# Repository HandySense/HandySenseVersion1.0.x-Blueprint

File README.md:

- 📫 VDO สอนใช้งาน HandySense: ...
[VDO_สอนใช้งาน_HandySense_Link_(คลิกเพื่อดู)](https://www.youtube.com/watch?v=b6W_hdBRJhI&list=PL7S9qslDc3W65hDXdvsPZP3AGufqoh_Rc&index=2&ab_channel=HandySenseOfficial) 

# HandySense Board 

* HandySense คือ ระบบอุปกรณ์ IOT สำหรับเกษตรอัจฉริยะที่สามารถแสดงค่าข้อมูล ปัจจัยในการควบคุมผลผลิตทางการเกษตร โดยใช้เทคโนโลยีเซนเซอร์เข้ามาช่วยในกระบวนการเพาะปลูกซึ่งช่วยให้เกษตรกรสามารถควบคุมสภาวะแวดล้อมในการปลูกได้ตั้งแต่เริ่มต้นส่งผลให้สามารถควบคุมคุณภาพและประเมินปริมาณผลผลิต 
* รวมถึงช่วยเรื่องการเพิ่มคุณค่าของผลผลิตได้โดยใช้การควบคุมกระบวนการเพาะปลูกเพื่อให้ผลผลิตออกในช่วงที่มีความต้องการหรือผลผลิตขาดแคลนรวมถึงการช่วยเกษตรกรนำองค์ความรู้ที่เกิดจากทักษะที่ไม่สามารถถ่ายทอดให้เข้าใจได้เนื่องจากเป็นภูมิปัญญาและเป็นการทำเกษตรกรรมแบบวิถีชาวบ้านโดยการลองผิดลองถูกหรือเป็นองค์ความรู้ที่สืบทอดต่อกัน
 
สารบัญ (Table of contents)
=========================

<!--ts-->
   * [Descriptions](#descriptions)
     องค์ประกอบของบอร์ด HandySense 
   * [Schematic](#schematic)
     ไฟล์ .brd (PCB  layout) และ .sch
   * [Blueprint](#blueprint)
     (GerberFile)
   * [BOM](#bom)
     รายการอุปกรณ์อิเล็กทรอนิกส์ BOM (bill of material)
   * [Manual](#manual)
     คู่มือการใช้งาน 
<!--te-->

Descriptions
===========
### องค์ประกอบของบอร์ด-HandySense 

โดย HandySense Board ประกอบด้วยอินเตอร์เฟสการสื่อสารหลักเป็น I2C, SPI, Analog, WIFI 
* I2C ต่อ Connector ออกมาให้ใช้งาน 2 ชุด (+5V)  
* Analog ต่อ Connector ออกมาให้ใช้งาน 3 pin ได้แก่ IO36(A0), IO39(A3), IO32(A4)
* SPI ขา CS/SS เป็น IO5 บนบอร์ดไม่ได้ต่ออุปกรณ์ แต่ต่อกับ IDC10 (block 10 pin) 
* ส่วน WIFI สื่อสารข้อมูลกับ Server เป็นหลัก
* Output เป็น Relay 220V AC 10A โดยต่อ pin ได้แก่ IO25, IO4, IO12, IO13 

* รายละเอียดแสดงดังภาพ (*แสดงพอสังเขป โดยรายละเอียดอ่านคู่มือเพิ่มเติม)

Schematic
===========
### ไฟล์ .brd (PCB  layout) และ .sch
สำหรับ HandySense version นี้ออกแบบด้วยโปรแกรม Autodesk Eagle ซึ่งไฟล์สามารถกดดาวน์โหลดได้ด้านบน 

* ไฟล์ .brd (PCB  layout) และ .sch

Blueprint
===========
### Gerber File
สำหรับ BluePrint จะ save เป็น Gerber File ที่สามารถนำไปสั่งผลิตได้ โดยไม่ต้องปรับแก้อะไร สามารถดาวน์โหลดได้ด้านบน

* Gerber File 

BOM
===========
### รายการอุปกรณ์อิเล็กทรอนิกส์ BOM (Bill Of Material)
* สำหรับรายการอุปกรณ์อิเล็กทรอนิกส์ของบอร์ด HandySense มีรายการทั้งหมดอยู่ในไฟล์ ชื่อ HandySense_v1.0.2_BOM.ods (เปิดดูด้วยโปรแกรม MS Excel)
ซึ่งจะบอกรายละเอียดที่จำเป็นและราคาต่อบอร์ดหรือราคารวมคร่าว ๆ ได้ (อาจจะมี +,- เนื่องจากราคามีการอับเดตเป็นช่วง ๆ ขึ้นอยู่กับผู้ขาย) สามารถที่จะระบุจำนวนบอร์ดที่ต้องการได้ในช่อง

* BOM (Bill Of Material)

Manual
===========
### คู่มือการใช้งาน 
* สำหรับคู่มือการใช้งาน จะประกอบไปด้วย 2 เล่ม ได้แก่ 
* คู่มือสอนใช้งานบอร์ด HandySense
* คู่มือสอนใช้งาน HandySense Dashboard 

# Open Hardware Facts

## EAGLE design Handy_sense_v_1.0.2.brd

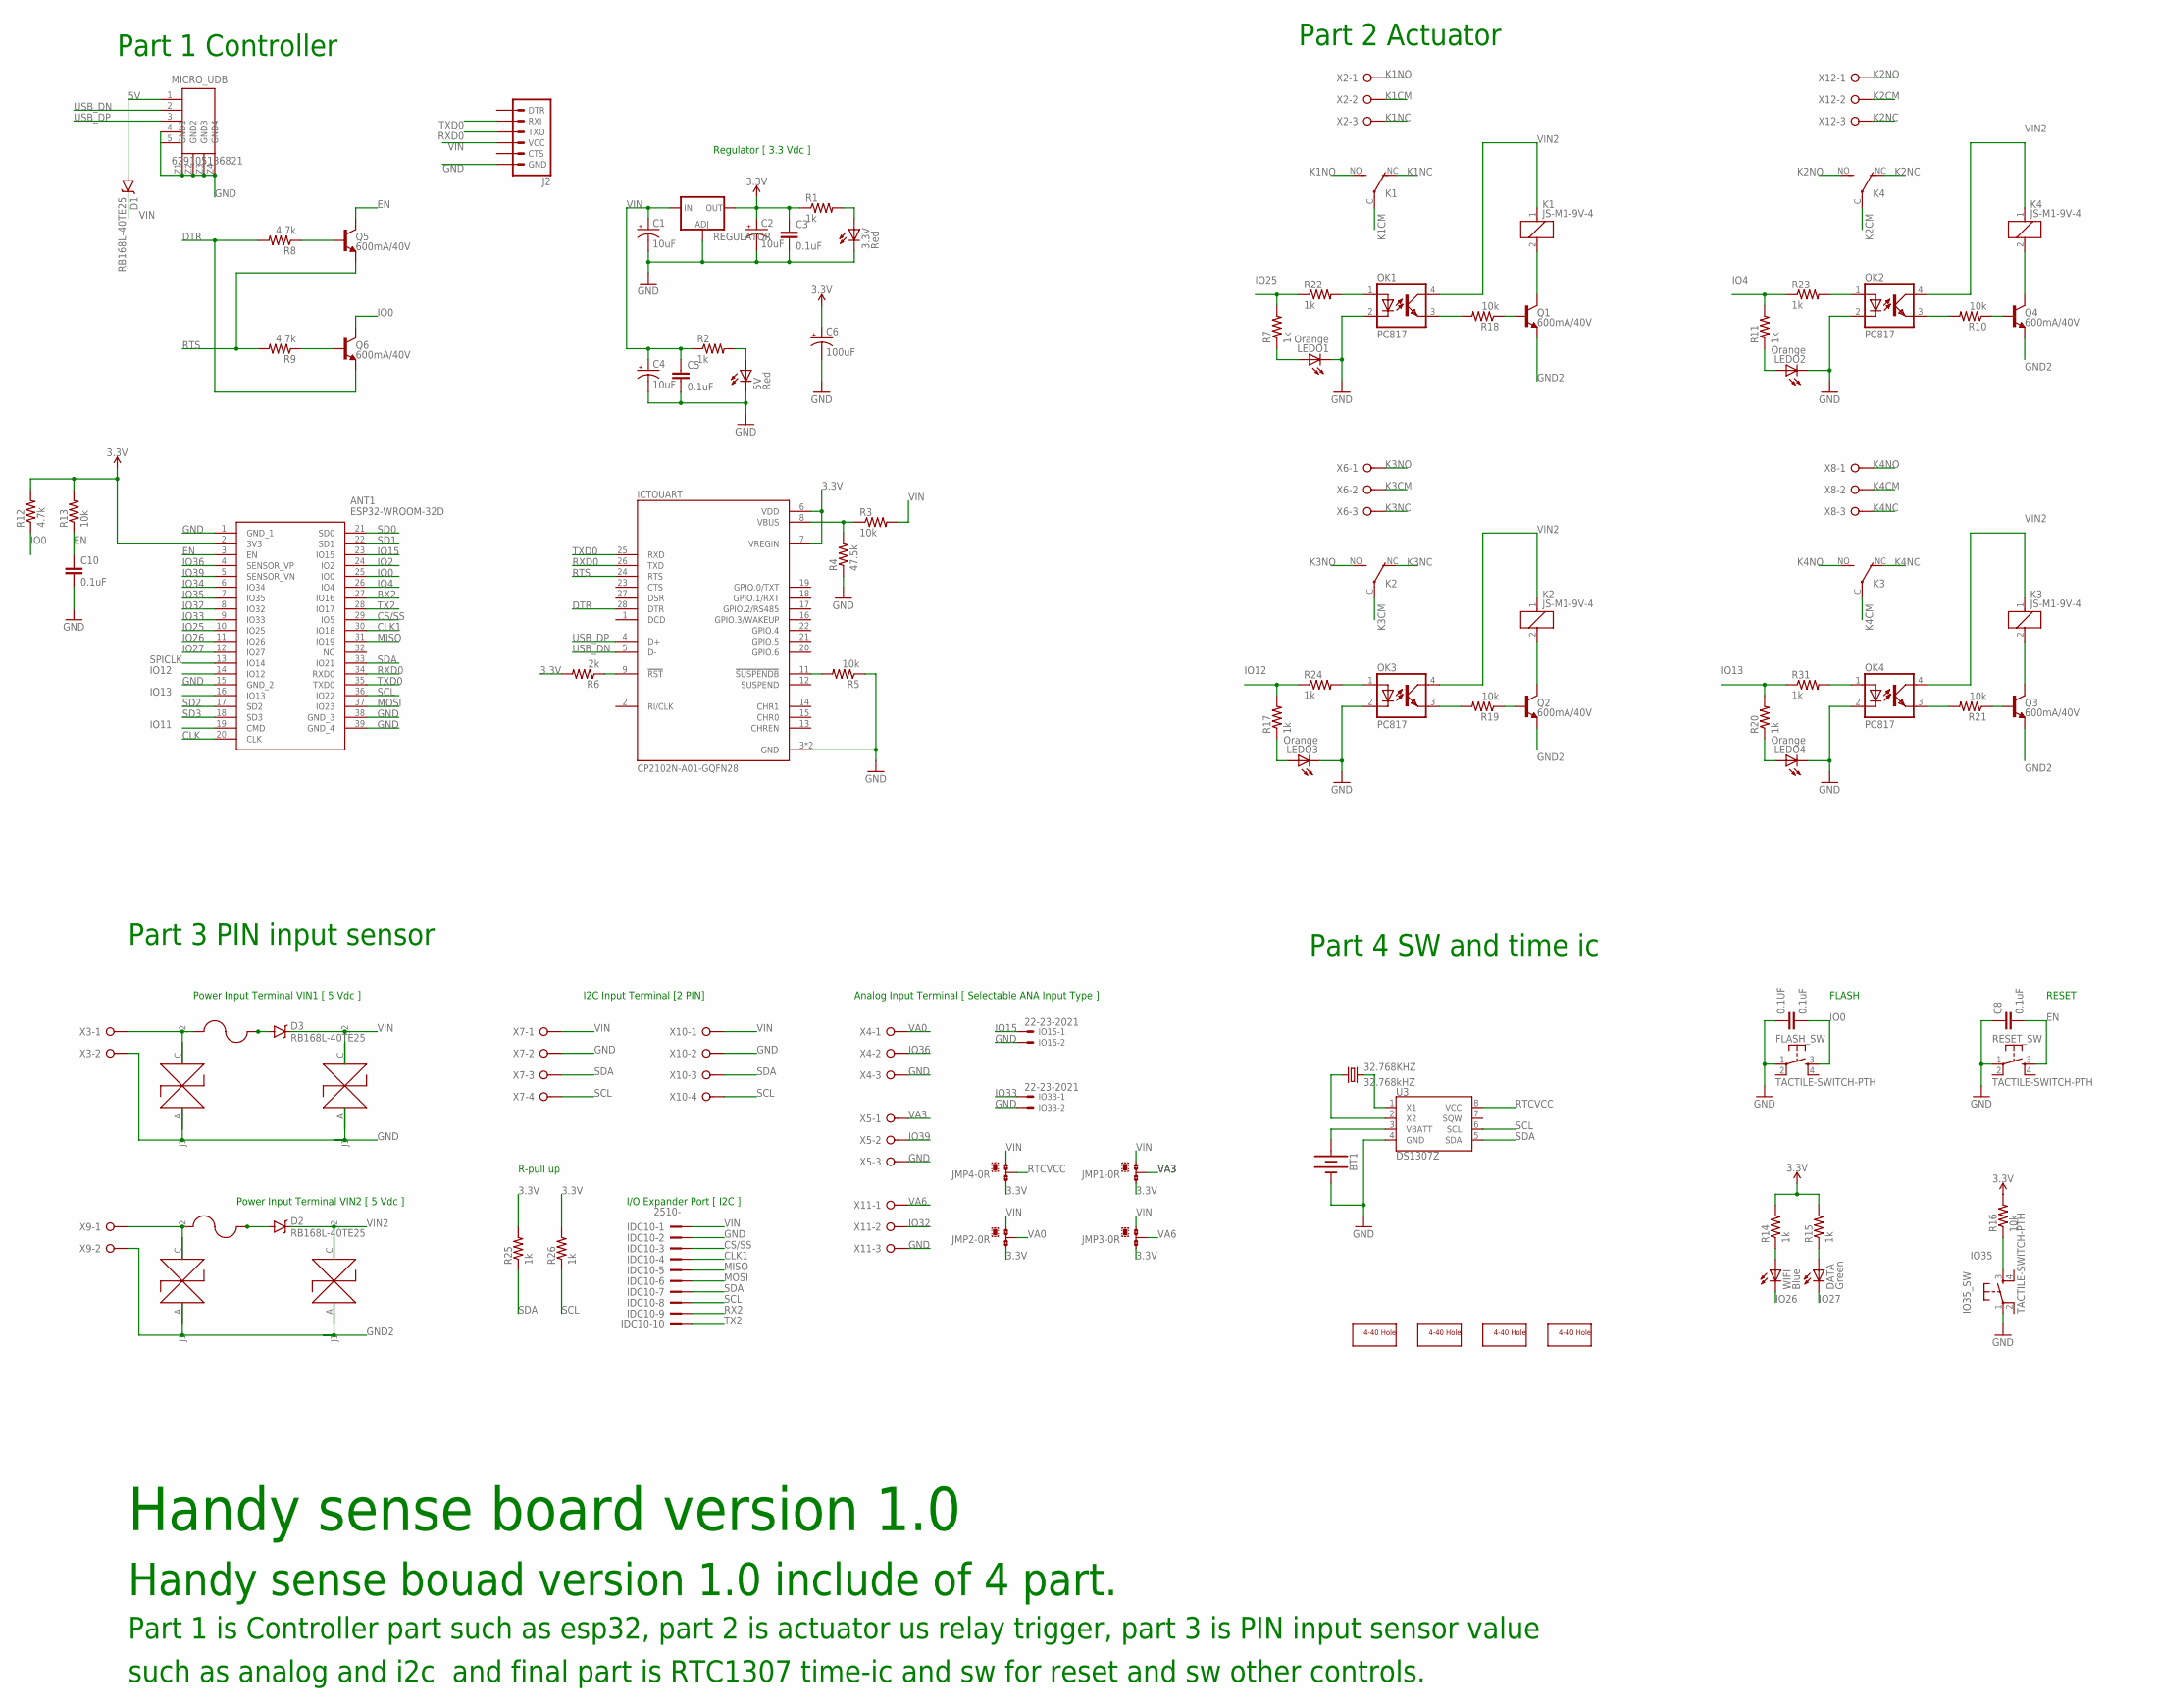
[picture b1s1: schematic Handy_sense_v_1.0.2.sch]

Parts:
0.1UF: 0.1uF; 0805
3.3V, 5V: Red; CHIPLED_0805
32.768KHZ: 32.768kHZ; TC26H
ANT1: ESP32-WROOM-32D; ESP32WROOM32D
BT1: BATTERY-20MM_PTH_KIT; BATTCOM_20MM_PTH_KIT
C1, C2, C4: 10uF; EIA3216
C3, C5, C8, C10: 0.1uF; 0805
C6: 100uF; EIA7343
D1, D2, D3: RB168L-40TE25; SMA-DIODE
DATA: Green; CHIPLED_0805
FLASH_SW: TACTILE-SWITCH-PTH; TAC-SWITCH-PTH
HOLE0, HOLE1, HOLE2, HOLE3: SCREW_HOLE_4-40
ICTOUART: CP2102N-A01-GQFN28; QFN50P500X500X80-29N
IDC10: 2510-; PAK100/2500-10
IO15, IO33: 22-23-2021
IO35_SW: TACTILE-SWITCH-PTH; TAC-SWITCH-PTH
J2: 6_PIN_SERIAL_TARGET_SILK; 1X06
J28CA1, J28CA3, J28CA4, J28CA6: SMBJ28CA; DIOM505270X240
JMP1, JMP2, JMP3, JMP4: 0R-JUMPB; B0R-JMP
K1, K2, K3, K4: JS-M1-9V-4; JS-M
LEDO1, LEDO2, LEDO3, LEDO4: Orange; CHIPLED_0805
MICRO_UDB: 629105136821
OK1, OK2, OK3, OK4: PC817; DIL04
Q1, Q2, Q3, Q4, Q5, Q6: 600mA/40V; SOT23-3
R1, R2, R7, R11, R14, R15, R17, R20, R22, R23, R24, R25, R26, R31: 1k; R0805
R3, R5, R10, R13, R16, R18, R19, R21: 10k; R0805
R4: 47.5k; R0805
R6: 2k; R0805
R8, R9, R12: 4.7k; R0805
REGULATOR: V_REG_LM1117SOT223; SOT223
RESET_SW: TACTILE-SWITCH-PTH; TAC-SWITCH-PTH
U3: DS1307Z; SO08-0.15
U$1, U$2: MSMFF2602; FUSE_MF-MSMF260-2
WIFI: Blue; CHIPLED_0805
X2, X4, X5, X6, X8, X11, X12: W237-03P; W237-133
X3, X9: W237-02P; W237-132
X7, X10: W237-04P; W237-4P

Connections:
3.3V: ANT1.2 (3V3), C2.A (+), C3.1, C6.A (+), ICTOUART.6 (VDD), ICTOUART.7 (VREGIN), JMP1.3, JMP2.3, JMP3.3, JMP4.3, R1.1, R6.2, R12.2, R13.2, R14.2, R15.2, R16.2, R25.2, R26.2, REGULATOR.2 (OUT), REGULATOR.4 (OUT)
5V: D1.A, MICRO_UDB.1 (+5V)
CLK: ANT1.20 (CLK)
CLK1: ANT1.30 (IO18), IDC10.4
CS/SS: ANT1.29 (IO5), IDC10.3
DTR: ICTOUART.28 (DTR), Q6.2 (E), R8.2
EN: ANT1.3 (EN), C8.2, C10.1, Q5.3 (C), R13.1, RESET_SW.3
GND: 0.1UF.1, 3.3V.C, 5V.C, ANT1.1 (GND_1), ANT1.15 (GND_2), ANT1.38 (GND_3), ANT1.39 (GND_4), BT1.2 (-), C1.C (-), C2.C (-), C3.2, C4.C (-), C5.2, C6.C (-), C8.1, C10.2, FLASH_SW.1, ICTOUART.3 (GND), ICTOUART.29 (GND), IDC10.2, IO15.2, IO33.2, IO35_SW.1, J2.6 (GND), J28CA1.A (J1), J28CA3.A (J1), LEDO1.C, LEDO2.C, LEDO3.C, LEDO4.C, MICRO_UDB.4 (ID), MICRO_UDB.5 (GND), MICRO_UDB.Z1 (GND1), MICRO_UDB.Z2 (GND2), MICRO_UDB.Z3 (GND3), MICRO_UDB.Z4 (GND4), OK1.2 (C), OK2.2 (C), OK3.2 (C), OK4.2 (C), R4.1, R5.1, REGULATOR.1 (ADJ), RESET_SW.1, U3.4 (GND), X3.2, X4.3, X5.3, X7.2, X10.2, X11.3
GND2: J28CA4.A (J1), J28CA6.A (J1), Q1.2 (E), Q2.2 (E), Q3.2 (E), Q4.2 (E), X9.2
IO0: 0.1UF.2, ANT1.25 (IO0), FLASH_SW.3, Q6.3 (C), R12.1
IO2: ANT1.24 (IO2)
IO4: ANT1.26 (IO4), R11.2, R23.1
IO11: ANT1.19 (CMD)
IO12: ANT1.14 (IO12), R17.2, R24.1
IO13: ANT1.16 (IO13), R20.2, R31.1
IO15: ANT1.23 (IO15), IO15.1
IO25: ANT1.10 (IO25), R7.2, R22.1
IO26: ANT1.11 (IO26), WIFI.C
IO27: ANT1.12 (IO27), DATA.C
IO32: ANT1.8 (IO32), X11.2
IO33: ANT1.9 (IO33), IO33.1
IO34: ANT1.6 (IO34)
IO35: ANT1.7 (IO35), IO35_SW.3, R16.1
IO36: ANT1.4 (SENSOR_VP), X4.2
IO39: ANT1.5 (SENSOR_VN), X5.2
K1CM: K1.C, X2.2
K1NC: K1.NC (O), X2.3
K1NO: K1.NO (S), X2.1
K2CM: K4.C, X12.2
K2NC: K4.NC (O), X12.3
K2NO: K4.NO (S), X12.1
K3CM: K2.C, X6.2
K3NC: K2.NC (O), X6.3
K3NO: K2.NO (S), X6.1
K4CM: K3.C, X8.2
K4NC: K3.NC (O), X8.3
K4NO: K3.NO (S), X8.1
MISO: ANT1.31 (IO19), IDC10.5
MOSI: ANT1.37 (IO23), IDC10.6
unnamed: K1.2, Q1.3 (C)
unnamed: ICTOUART.9 (!RST), R6.1
unnamed: ICTOUART.8 (VBUS), R3.1, R4.2
unnamed: 5V.A, R2.2
unnamed: Q4.1 (B), R10.1
unnamed: ICTOUART.11 (!SUSPENDB), R5.2
unnamed: Q5.1 (B), R8.1
unnamed: Q1.1 (B), R18.1
unnamed: Q2.1 (B), R19.1
unnamed: Q6.1 (B), R9.1
unnamed: OK3.3 (EMIT), R19.2
unnamed: OK1.3 (EMIT), R18.2
unnamed: 32.768KHZ.2, U3.1 (X1)
unnamed: R14.1, WIFI.A
unnamed: 3.3V.A, R1.2
unnamed: K2.2, Q2.3 (C)
unnamed: 32.768KHZ.1, U3.2 (X2)
unnamed: BT1.1 (+), U3.3 (VBATT)
unnamed: DATA.A, R15.1
unnamed: LEDO2.A, R11.1
unnamed: OK2.3 (EMIT), R10.2
unnamed: LEDO3.A, R17.1
unnamed: K4.2, Q4.3 (C)
unnamed: Q3.1 (B), R21.1
unnamed: LEDO4.A, R20.1
unnamed: OK4.3 (EMIT), R21.2
unnamed: K3.2, Q3.3 (C)
unnamed: J28CA1.C (J2), U$1.1, X3.1
unnamed: OK1.1 (A), R22.2
unnamed: OK3.1 (A), R24.2
unnamed: OK2.1 (A), R23.2
unnamed: OK4.1 (A), R31.2
unnamed: LEDO1.A, R7.1
unnamed: D3.A, U$1.2
unnamed: J28CA4.C (J2), U$2.1, X9.1
unnamed: D2.A, U$2.2
RTCVCC: JMP4.2, U3.8 (VCC)
RTS: ICTOUART.24 (RTS), Q5.2 (E), R9.2
RX2: ANT1.27 (IO16), IDC10.9
RXD0: ANT1.34 (RXD0), ICTOUART.26 (TXD), J2.3 (TXO)
SCL: ANT1.36 (IO22), IDC10.8, R26.1, U3.6 (SCL), X7.4, X10.4
SD0: ANT1.21 (SD0)
SD1: ANT1.22 (SD1)
SD2: ANT1.17 (SD2)
SD3: ANT1.18 (SD3)
SDA: ANT1.33 (IO21), IDC10.7, R25.1, U3.5 (SDA), X7.3, X10.3
SPICLK: ANT1.13 (IO14)
TX2: ANT1.28 (IO17), IDC10.10
TXD0: ANT1.35 (TXD0), ICTOUART.25 (RXD), J2.2 (RXI)
USB_DN: ICTOUART.5 (D-), MICRO_UDB.2 (D-)
USB_DP: ICTOUART.4 (D+), MICRO_UDB.3 (D+)
VA0: JMP2.2, X4.1
VA3: JMP1.2, X5.1
VA6: JMP3.2, X11.1
VIN: C1.A (+), C4.A (+), C5.1, D1.C, D3.C, IDC10.1, J2.4 (VCC), J28CA3.C (J2), JMP1.1, JMP2.1, JMP3.1, JMP4.1, R2.1, R3.2, REGULATOR.3 (IN), X7.1, X10.1
VIN2: D2.C, J28CA6.C (J2), K1.1, K2.1, K3.1, K4.1, OK1.4 (COL), OK2.4 (COL), OK3.4 (COL), OK4.4 (COL)

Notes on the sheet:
Power Input Terminal VIN1 [ 5 Vdc ]
I/O Expander Port [ I2C ]
Analog Input Terminal [ Selectable ANA Input Type ]
Regulator [ 3.3 Vdc ]
FLASH
RESET
Power Input Terminal VIN2 [ 5 Vdc ]
I2C Input Terminal [2 PIN]
R-pull up
Handy sense board version 1.0
Handy sense bouad version 1.0 include of 4 part.
Part 1 Controller
Part 2 Actuator
Part 3 PIN input sensor
Part 4 SW and time ic
Part 1 is Controller part such as esp32, part 2 is actuator us relay trigger, part 3 is PIN input sensor value
such as analog and i2c and final part is RTC1307 time-ic and sw for reset and sw other controls.

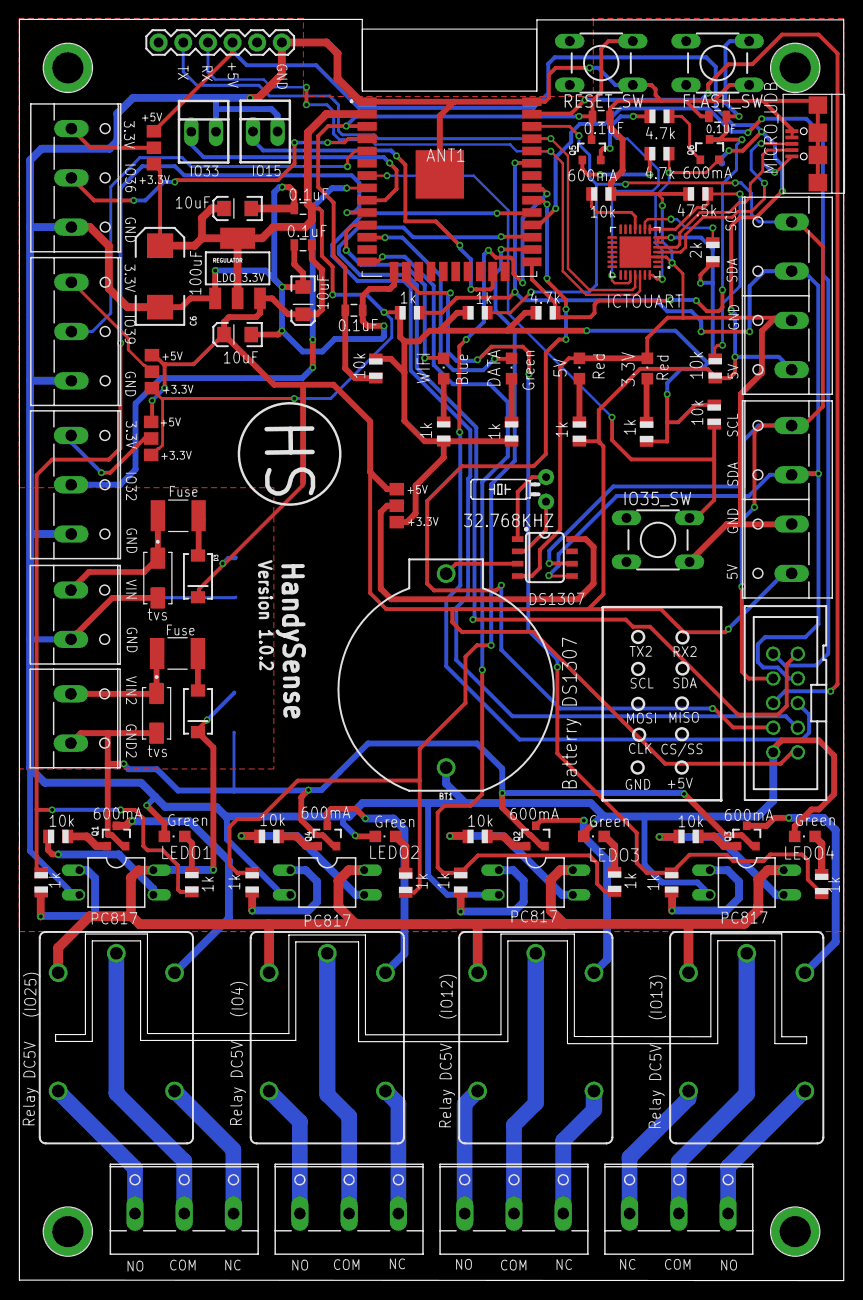
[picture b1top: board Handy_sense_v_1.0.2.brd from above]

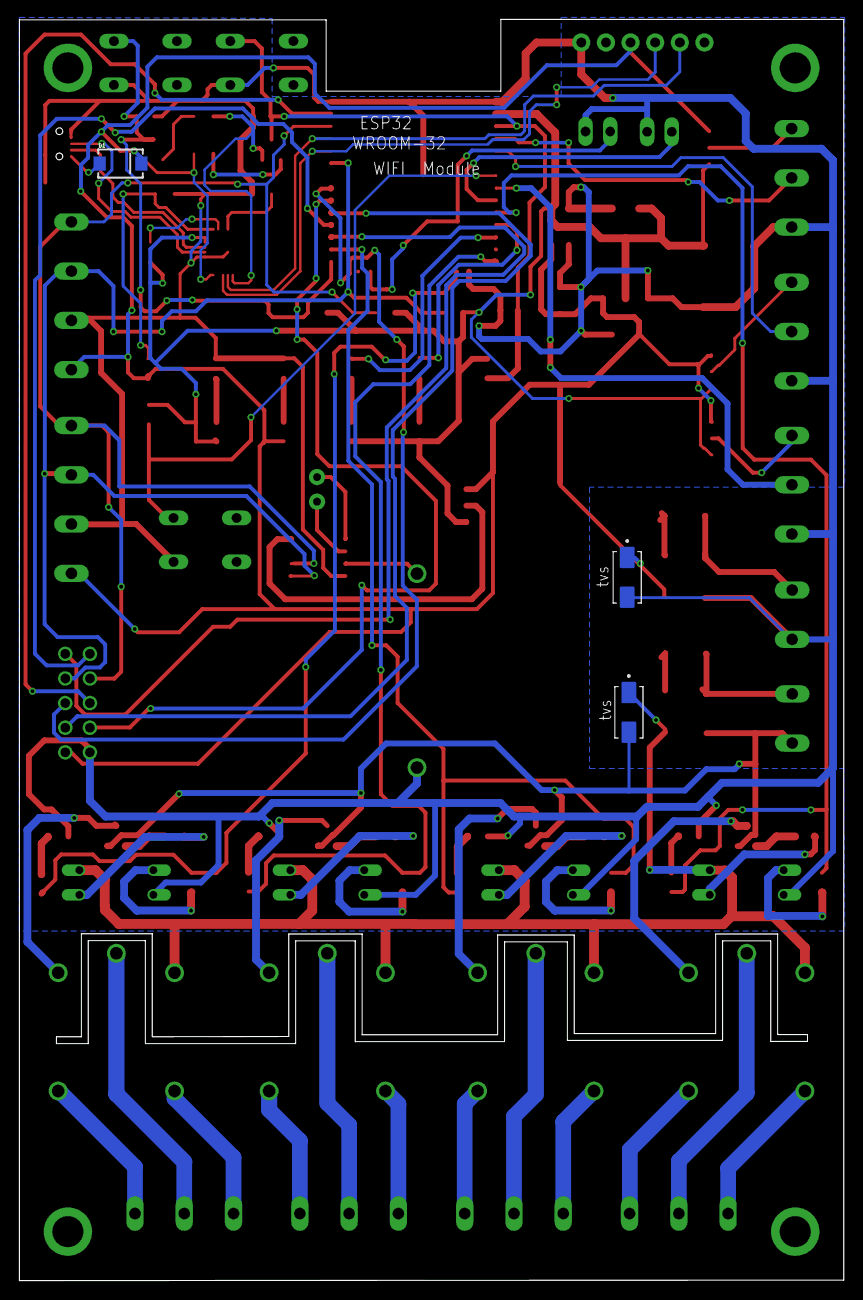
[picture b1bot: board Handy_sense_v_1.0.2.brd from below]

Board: 2 copper layers, 85.0 x 130.1 mm, 100 parts (3 on the bottom side), 86 nets.

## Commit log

2021-03-19 HandySense Version 1.0
    include
    - ฺBluePrint, schematic, PCB layout
    - BOM
    - Firmware
    - Dashboard
    - How to use
2021-03-19 Change URL HandySense
    https://dashboard.handysense.io/
2021-03-19 Upload Logo HandySense
2021-03-19 del demo phpMyadmin
2021-03-24 rename_folder
2021-03-24 rename HandySense
2021-04-19 ีupdate BOM
2021-05-11 Create LICENSE
2021-05-12 ีUpdate doc
2021-06-25 update BOM
2021-06-25 Update data
2021-08-17 ๊Update
2021-09-16 Update version
    - change tvs
    - add 3.3 V and 5V
    - change micro use
2021-09-16 new version 1.0.2
2021-09-27 update p1

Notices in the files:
parts and their libraries:
SparkFun-Batteries: Licensing: Creative Commons ShareAlike 4.0 International - https://creativecommons.org/licenses/by-sa/4.0
Wurth_Input-Output_Connectors_rev15d: Copyright: Würth Elektronik
